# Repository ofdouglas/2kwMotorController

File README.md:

# 2kwMotorController
2 kilowatt brushed DC motor controller

This is a senior design project in Electrical and Computer Engineering at George Mason University.

All works are copyrighted by their respective authors.

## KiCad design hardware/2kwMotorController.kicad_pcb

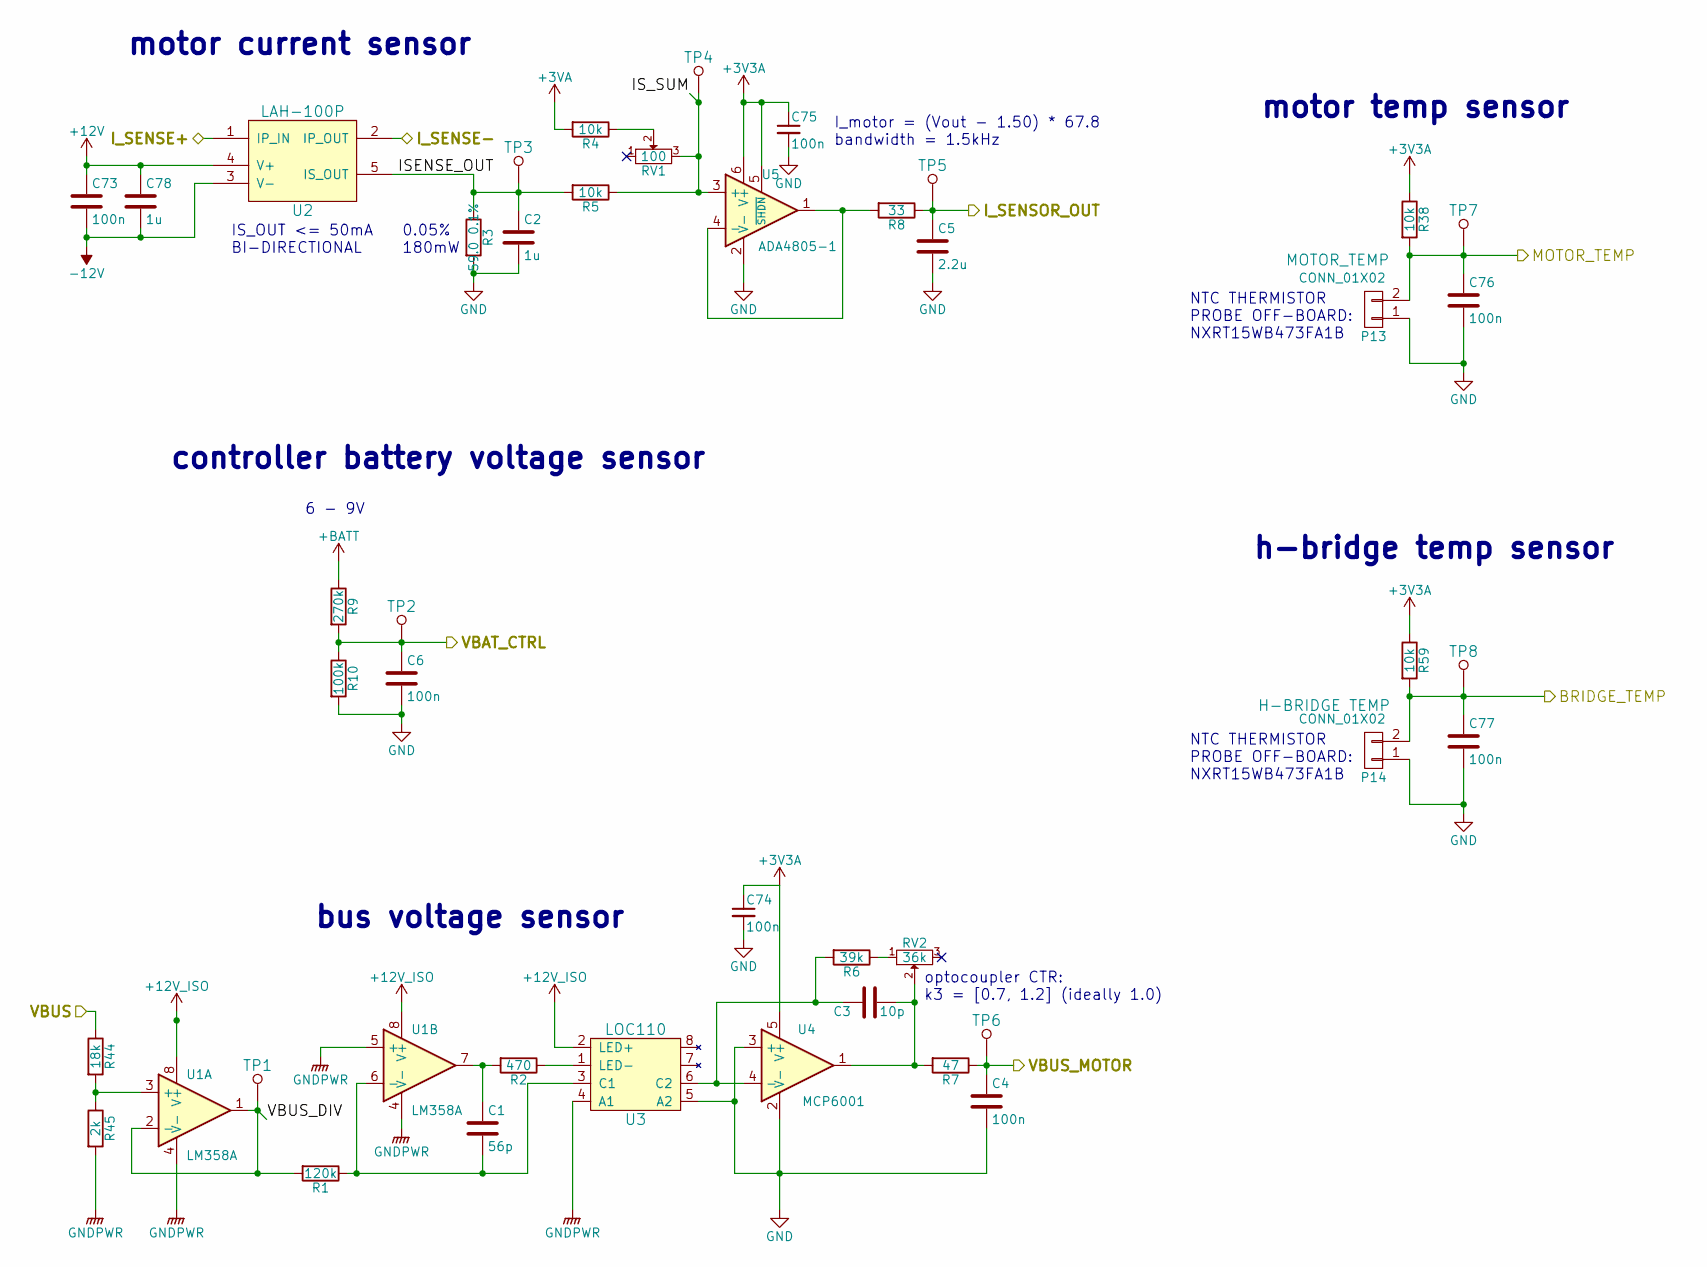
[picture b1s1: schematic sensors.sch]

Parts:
C1: 56p; C_0603; Voltage 16V
C2: 1u; C_0603; Voltage 16V
C3: 10p; C_0603; Voltage 16V
C4, C6, C74, C75, C76, C77: 100n; C_0603; Voltage 16V
C5: 2.2u; C_0603; Voltage 16V
C73: 100n; C_0603; Voltage 25V
C78: 1u; C_0603; Voltage 25V
P13, P14: CONN_01X02; Pin_Header_Straight_1x02
R1: 120k; R_0603
R2: 470; R_0603
R3: 59.0 0.1%; R_1206
R4, R5, R38, R59: 10k; R_0603
R6: 39k; R_0603
R7: 47; R_0603
R8: 33; R_0603
R9: 270k; R_0603
R10: 100k; R_0603
R44: 18k; R_0603
R45: 2k; R_0603
RV1: 100; Trimpot-23B
RV2: 36k; Trimpot-23B
TP1, TP2, TP3, TP4, TP5, TP6, TP7, TP8: TEST_POINT; TEST_PAD_1.27mm
U1: LM358A; SOIC-8_3.9x4.9mm_Pitch1.27mm
U2: LAH-100P; LAH_100-P
U3: LOC110; DIP-8_SMD
U4: MCP6001; SC-70-5
U5: ADA4805-1; SOT-23-6

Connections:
+3V3A: C74.1, C75.1, R38.1, R59.1, U4.5 (V+), U5.5 (~SHDN), U5.6 (V+); also elsewhere on the board
+3VA: R4.2; also elsewhere on the board
+12V: C73.1, C78.1, U2.4 (V+); also elsewhere on the board
+12V_ISO: U1.8 (V+), U3.2 (LED+); also elsewhere on the board
+BATT: R9.1; also elsewhere on the board
-12V: C73.2, C78.2, U2.3 (V-); also elsewhere on the board
/h-bridge/I_SENSE+: U2.1 (IP_IN); also elsewhere on the board
/h-bridge/I_SENSE-: U2.2 (IP_OUT); also elsewhere on the board
/h-bridge/VBUS: R44.1; also elsewhere on the board
/mcu/BRIDGE_TEMP: C77.1, P14.2, R59.2, TP8.1; also elsewhere on the board
/mcu/I_SENSOR_OUT: C5.1, R8.1, TP5.1; also elsewhere on the board
/mcu/MOTOR_TEMP: C76.1, P13.2, R38.2, TP7.1; also elsewhere on the board
/mcu/VBAT_CTRL: C6.1, R9.2, R10.1, TP2.1; also elsewhere on the board
/mcu/VBUS_MOTOR: C4.1, R7.1, TP6.1; also elsewhere on the board
/sensors/ISENSE_OUT: C2.1, R3.1, R5.2, TP3.1, U2.5 (IS_OUT)
/sensors/IS_SUM: R5.1, RV1.3, TP4.1, U5.3 (+)
/sensors/VBUS_DIV: R1.2, TP1.1, U1.1, U1.2 (-)
GND: C2.2, C4.2, C5.2, C6.2, C74.2, C75.2, C76.2, C77.2, P13.1, P14.1, R3.2, R10.2, U3.5 (A2), U4.2 (V-), U4.3 (+), U5.2 (V-); also elsewhere on the board
GNDPWR: R45.2, U1.4 (V-), U1.5 (+), U3.4 (A1); also elsewhere on the board
unnamed: C1.1, R2.2, U1.7
unnamed: C1.2, R1.1, U1.6 (-), U3.3 (C1)
unnamed: C3.1, R6.2, U3.6 (C2), U4.4 (-)
unnamed: C3.2, R7.2, RV2.2, U4.1
unnamed: R2.1, U3.1 (LED-)
unnamed: R4.1, RV1.2
unnamed: R6.1, RV2.1
unnamed: R8.2, U5.1, U5.4 (-)
unnamed: R44.2, R45.1, U1.3 (+)

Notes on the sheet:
IS_OUT <= 50mA BI-DIRECTIONAL
motor current sensor
h-bridge temp sensor
controller battery voltage sensor
bus voltage sensor
6 - 9V
optocoupler CTR: k3 = [0.7, 1.2] (ideally 1.0)
I_motor = (Vout - 1.50) * 67.8 bandwidth = 1.5kHz
0.05% 180mW
motor temp sensor
NTC THERMISTOR PROBE OFF-BOARD: NXRT15WB473FA1B

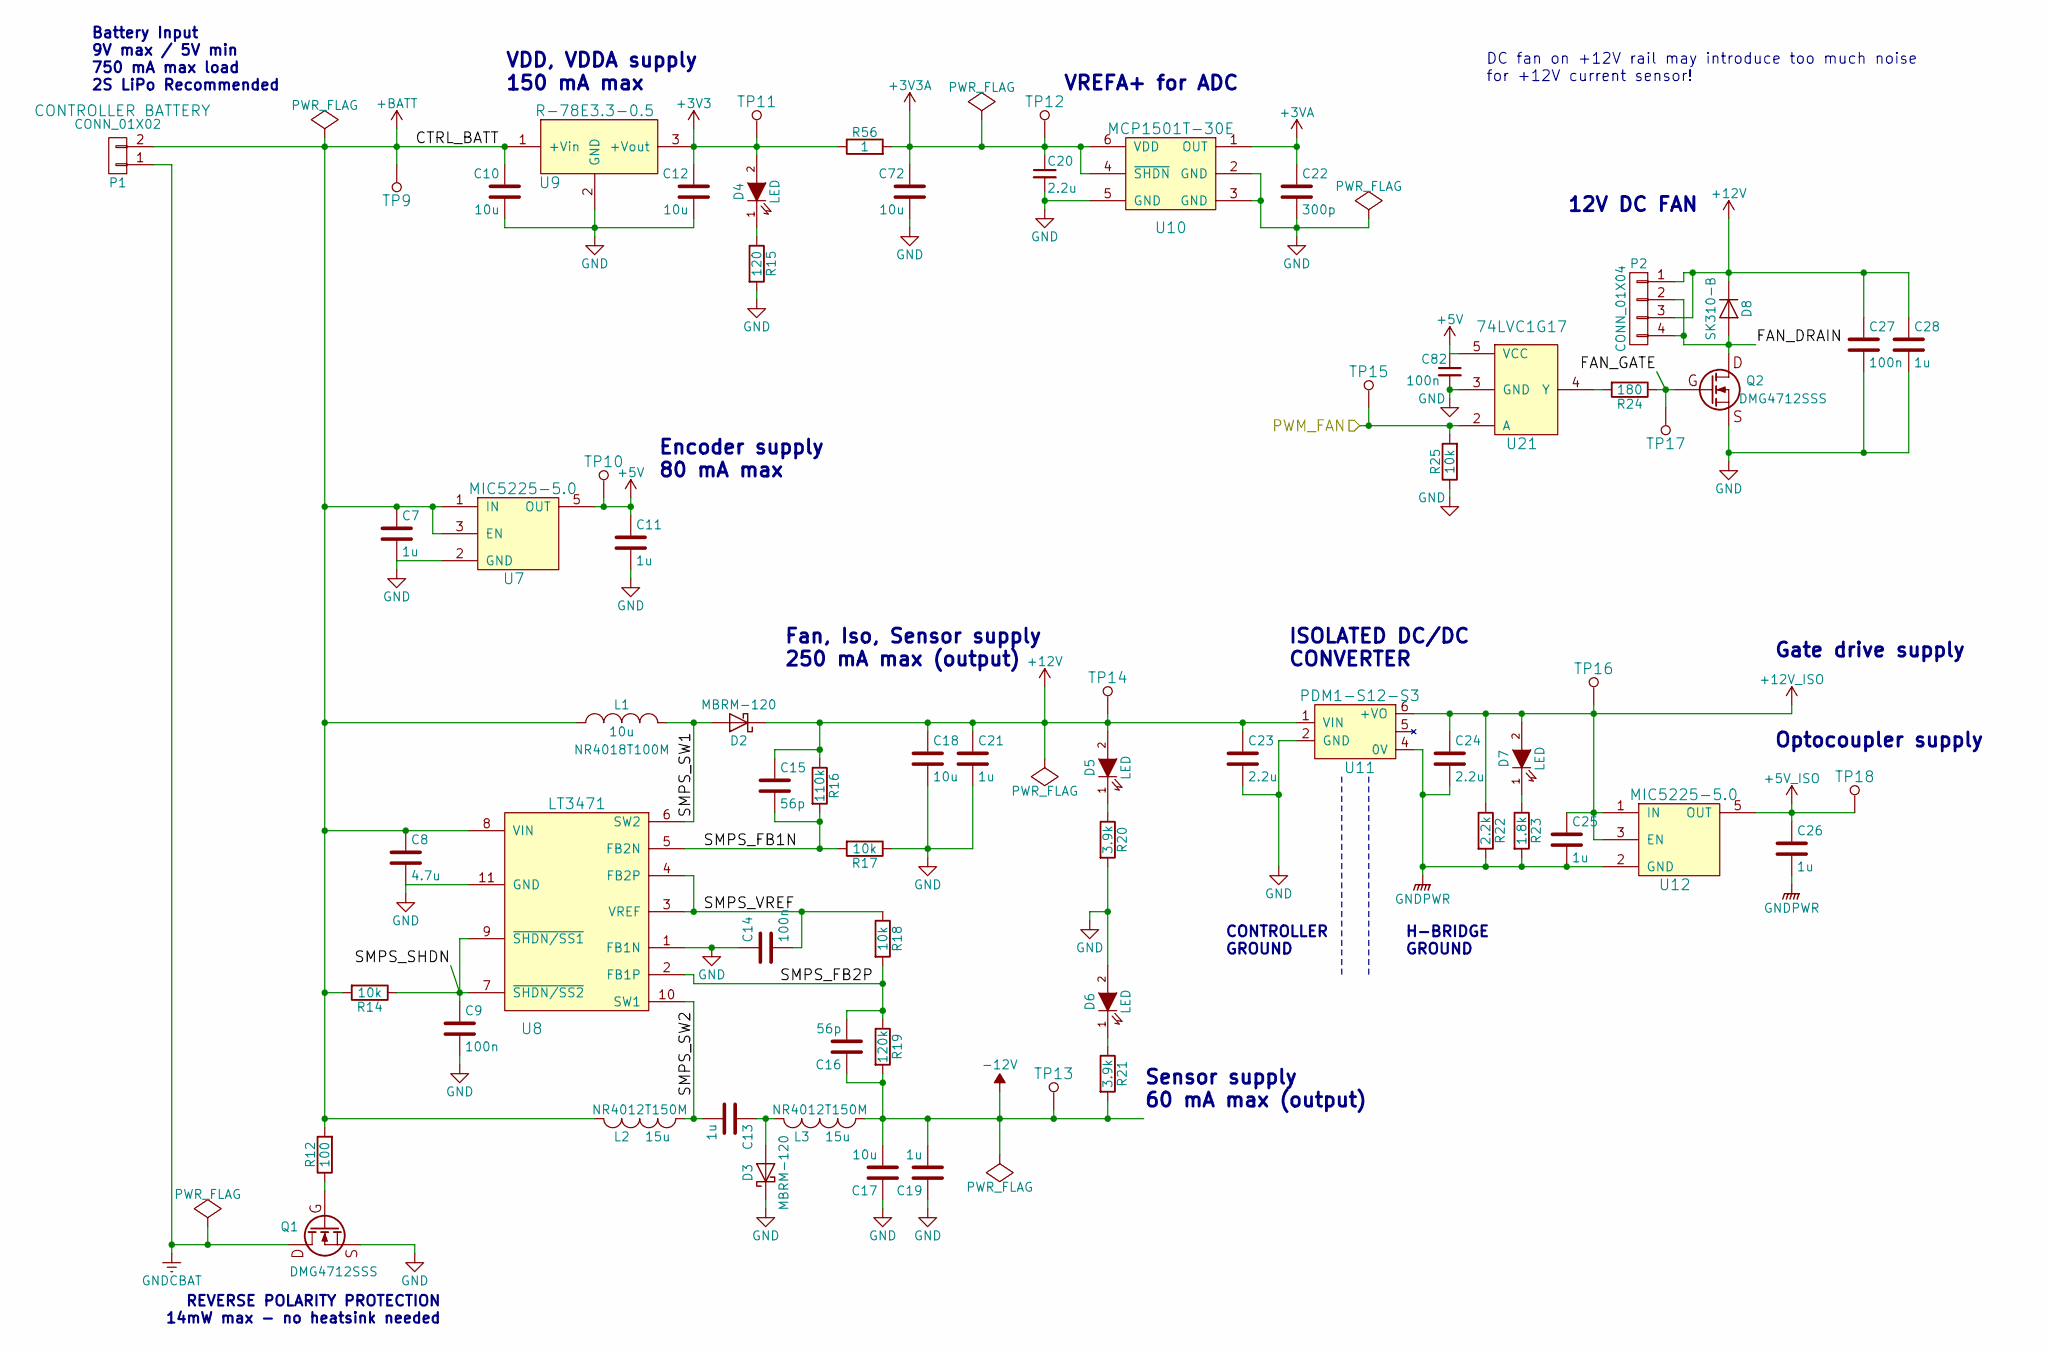
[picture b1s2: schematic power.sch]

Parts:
C7, C11: 1u; C_0603; Voltage 16V
C8: 4.7u; C_0603; Voltage 25V
C9, C14, C27, C82: 100n; C_0603; Voltage 25V
C10, C12, C72: 10u; C_0805; Voltage 16V
C13: 1u; C_0603
C15, C16: 56p; C_0603; Voltage 25V
C17, C18: 10u; C_0805; Voltage 25V
C19, C21, C25, C26, C28: 1u; C_0603; Voltage 25V
C20: 2.2u; C_0603; Voltage 16V
C22: 300p; C_0603; Voltage 16V
C23, C24: 2.2u; C_0603; Voltage 25V
D2, D3: MBRM-120; DIODE_POWERMITE
D4, D5, D6, D7: LED; LED_0603
D8: SK310-B; DIODE_POWERMITE
L1: 10u; INDUCTOR_NR40xx
L2, L3: 15u; INDUCTOR_NR40xx
P1: CONN_01X02; Pin_Header_Straight_1x02
P2: CONN_01X04; TERM_4P_2-4_1990025
Q1, Q2: DMG4712SSS; SOIC-8_3.9x4.9mm_Pitch1.27mm
R12: 100; R_0603
R14, R17, R18, R25: 10k; R_0603
R15: 120; R_0603
R16: 110k; R_0603
R19: 120k; R_0603
R20, R21: 3.9k; R_0603
R22: 2.2k; R_0603
R23: 1.8k; R_0603
R24: 180; R_0603
R56: 1; R_0603
TP9, TP10, TP11, TP12, TP13, TP14, TP15, TP16, TP17, TP18: TEST_POINT; TEST_PAD_1.27mm
U7, U12: MIC5225-5.0; SOT-23-5
U8: LT3471; DFN-10-1EP_3x3mm_Pitch0.5mm
U9: R-78E3.3-0.5; R-78E-0.5
U10: MCP1501T-30E; SOT-23-6
U11: PDM1-S12-S3; PDM2-S
U21: 74LVC1G17; SC-74A

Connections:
+3V3A: C20.1, C72.1, R56.2, TP12.1, U10.4 (~SHDN), U10.6 (VDD); also elsewhere on the board
+3VA: C22.1, U10.1 (OUT); also elsewhere on the board
+5V: C11.1, C82.1, TP10.1, U7.5 (OUT), U21.5 (VCC); also elsewhere on the board
+5V_ISO: C26.1, TP18.1, U12.5 (OUT); also elsewhere on the board
+12V: C15.1, C18.1, C21.1, C23.1, C27.1, C28.1, D2.1 (K), D5.2 (A), D8.1 (K), P2.1, P2.3, R16.1, TP14.1, U11.1 (VIN); also elsewhere on the board
+12V_ISO: C24.1, C25.1, D7.2 (A), R22.1, TP16.1, U11.6 (+VO), U12.1 (IN), U12.3 (EN); also elsewhere on the board
+BATT: C7.1, C8.1, C10.1, L1.1, L2.1, P1.2, R12.2, R14.2, TP9.1, U7.1 (IN), U7.3 (EN), U8.8 (VIN), U9.1 (+Vin); also elsewhere on the board
-12V: C16.1, C17.2, C19.2, L3.2, R19.2, R21.2, TP13.1; also elsewhere on the board
/mcu/PWM_FAN: R25.2, TP15.1, U21.2 (A); also elsewhere on the board
/power/FAN_DRAIN: D8.2 (A), P2.2, P2.4, Q2.5 (D), Q2.6 (D), Q2.7 (D), Q2.8 (D)
/power/FAN_GATE: Q2.4 (G), R24.1, TP17.1
/power/SMPS_FB1N: C15.2, R16.2, R17.2, U8.5 (FB2N)
/power/SMPS_FB2P: C16.2, R18.2, R19.1, U8.2 (FB1P)
/power/SMPS_SHDN: C9.1, R14.1, U8.7 (~SHDN/SS2), U8.9 (~SHDN/SS1)
/power/SMPS_SW1: D2.2 (A), L1.2, U8.6 (SW2)
/power/SMPS_SW2: C13.2, L2.2, U8.10 (SW1)
/power/SMPS_VREF: C14.2, R18.1, U8.3 (VREF), U8.4 (FB2P)
GND: C7.2, C8.2, C9.2, C10.2, C11.2, C12.2, C14.1, C17.1, C18.2, C19.1, C20.2, C21.2, C22.2, C23.2, C27.2, C28.2, C72.2, C82.2, D3.1 (K), D6.2 (A), Q1.1 (S), Q1.2 (S), Q1.3 (1), Q2.1 (S), Q2.2 (S), Q2.3 (1), R15.2, R17.1, R20.2, R25.1, U7.2 (GND), U8.1 (FB1N), U8.11 (GND), U9.2 (GND), U10.2 (GND), U10.3 (GND), U10.5 (GND), U11.2 (GND), U21.3 (GND); also elsewhere on the board
GNDCBAT: P1.1, Q1.5 (D), Q1.6 (D), Q1.7 (D), Q1.8 (D)
GNDPWR: C24.2, C25.2, C26.2, R22.2, R23.2, U11.4 (0V), U12.2 (GND); also elsewhere on the board
unnamed: C13.1, D3.2 (A), L3.1
unnamed: D4.1 (K), R15.1
unnamed: D5.1 (K), R20.1
unnamed: D6.1 (K), R21.1
unnamed: D7.1 (K), R23.1
unnamed: Q1.4 (G), R12.1
unnamed: R24.2, U21.4 (Y)

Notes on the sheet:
Battery Input 9V max / 5V min 750 mA max load 2S LiPo Recommended
REVERSE POLARITY PROTECTION 14mW max - no heatsink needed
H-BRIDGE GROUND
CONTROLLER GROUND
ISOLATED DC/DC CONVERTER
DC fan on +12V rail may introduce too much noise for +12V current sensor!
VREFA+ for ADC
VDD, VDDA supply 150 mA max
Fan, Iso, Sensor supply 250 mA max (output)
Sensor supply 60 mA max (output)
Optocoupler supply
Gate drive supply
Encoder supply 80 mA max
12V DC FAN

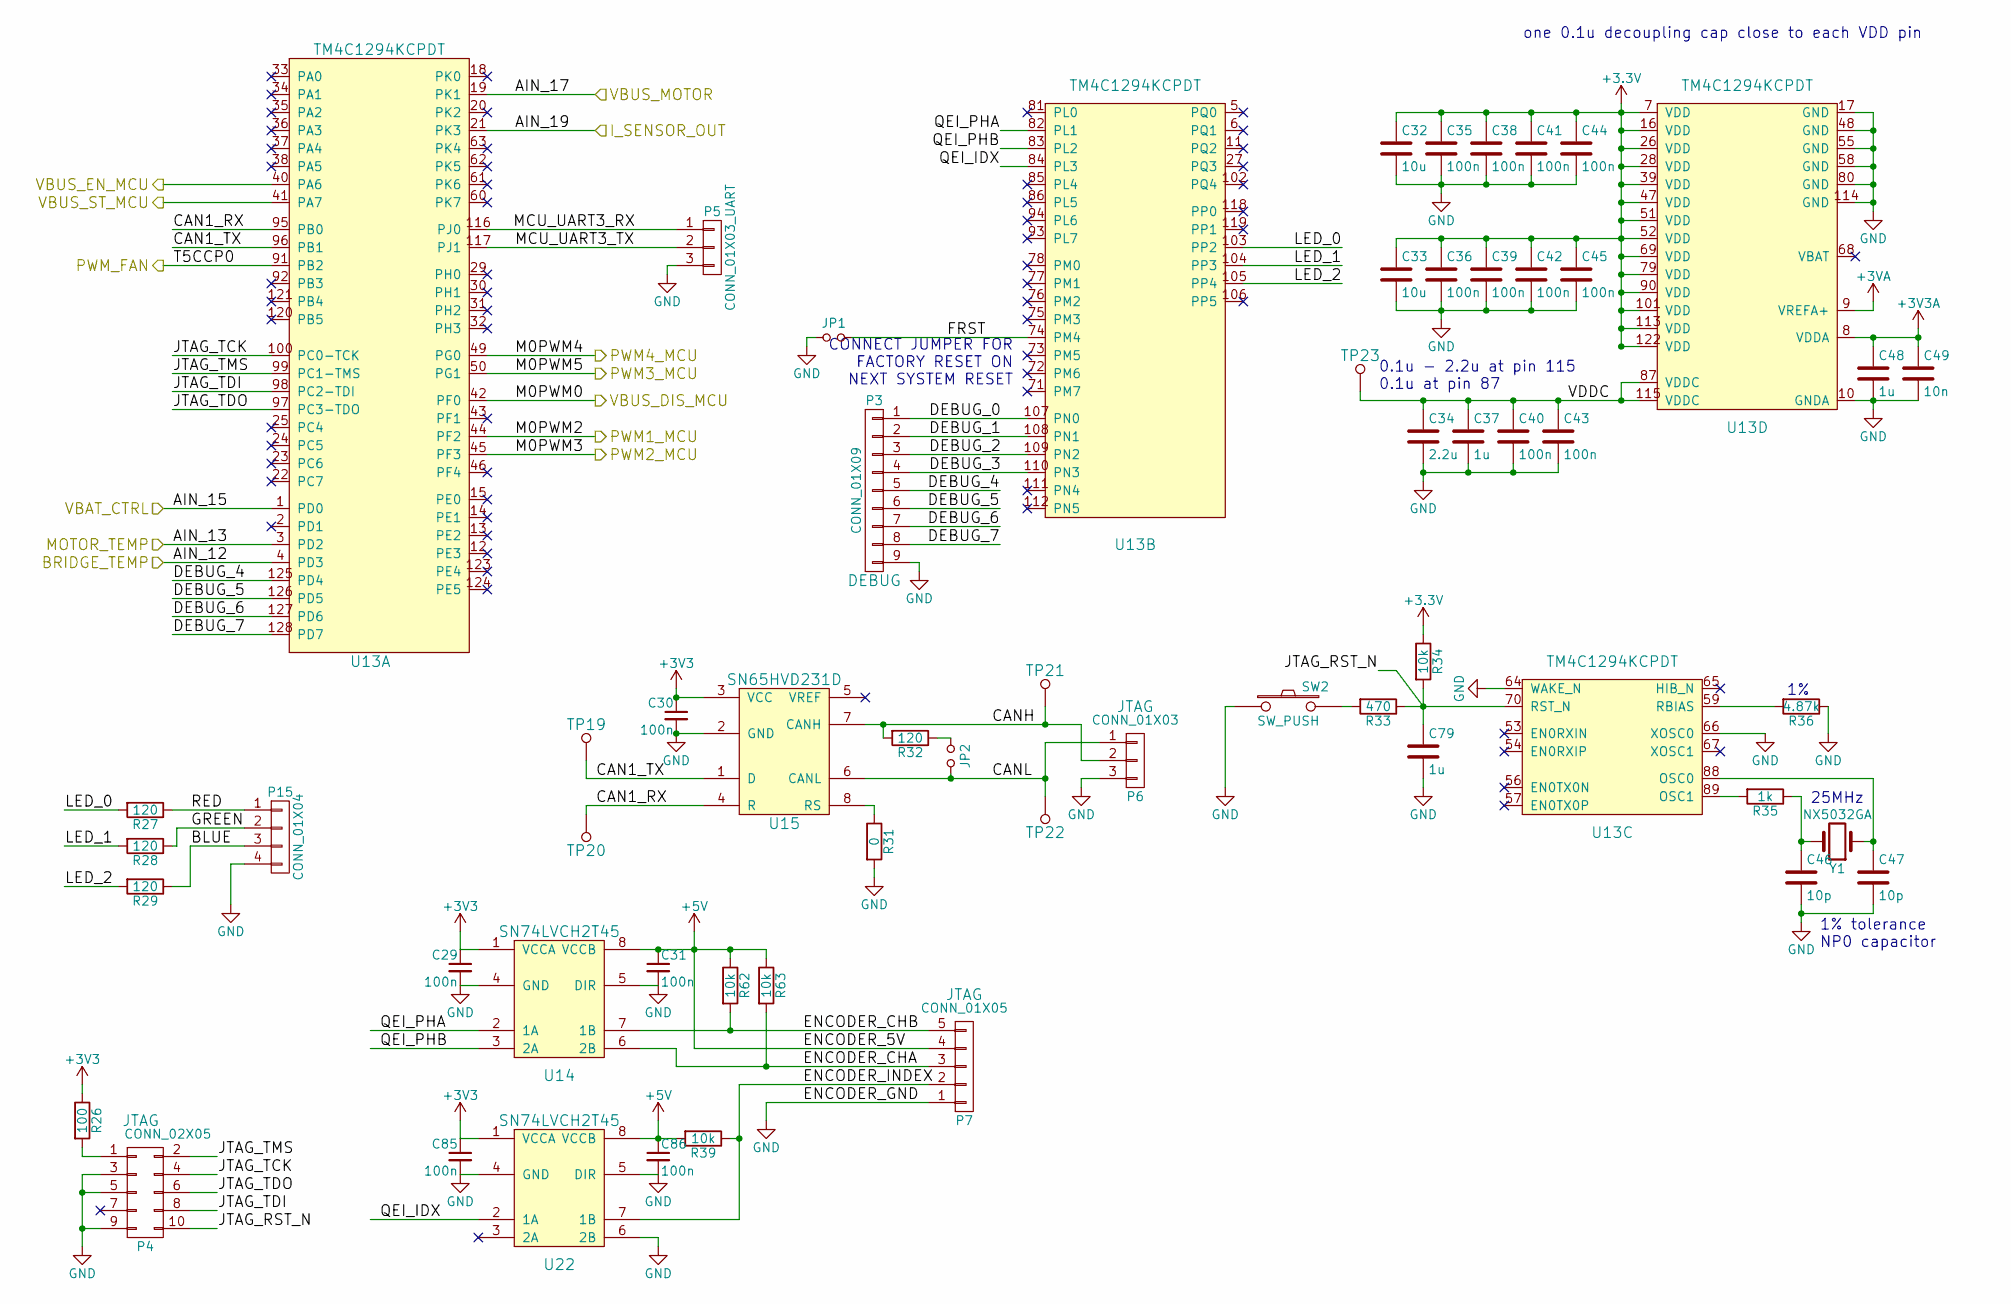
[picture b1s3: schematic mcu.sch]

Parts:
C29, C30, C31, C35, C36, C38, C39, C40, C41, C42, C43, C44, C45, C85, C86: 100n; C_0603; Voltage 16V
C32, C33: 10u; C_0805; Voltage 16V
C34: 2.2u; C_0603; Voltage 16V
C37, C48, C79: 1u; C_0603; Voltage 16V
C46, C47: 10p; C_0603; Voltage 16V
C49: 10n; C_0603; Voltage 16V
JP1, JP2: Jumper_NO_Small; Pin_Header_Straight_1x02
P3: CONN_01X09; Pin_Header_Straight_1x09
P4: CONN_02X05; Pin_Header_Straight_2x05_Pitch1.27mm
P5: CONN_01X03_UART; Pin_Header_Straight_1x03
P6: CONN_01X03; Pin_Header_Straight_1x03
P7: CONN_01X05; Pin_Header_Straight_1x05
P15: CONN_01X04; Pin_Header_Straight_1x04
R26: 100; R_0603
R27, R28, R29, R32: 120; R_0603
R31: 0; R_0603
R33: 470; R_0603
R34, R39, R62, R63: 10k; R_0603
R35: 1k; R_0603
R36: 4.87k; R_0603
SW2: SW_PUSH; SW_PUSH_SMALL
TP19, TP20, TP21, TP22, TP23: TEST_POINT; TEST_PAD_1.27mm
U13: TM4C1294KCPDT; TQFP-128_14x14mm_Pitch0.4mm_LONG
U14, U22: SN74LVCH2T45; MSOP-8_3x3mm_Pitch0.65mm
U15: SN65HVD231D; SOIC-8_3.9x4.9mm_Pitch1.27mm
Y1: NX5032GA; NX5032GA-CRYSTAL

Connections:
+3V3A: C48.1, C49.1, U13.8 (VDDA); also elsewhere on the board
+3VA: U13.9 (VREFA+); also elsewhere on the board
+5V: C31.1, C86.1, P7.4, R39.2, R62.1, R63.1, U14.8 (VCCB), U22.8 (VCCB); also elsewhere on the board
/h-bridge/PWM1_MCU: U13.44 (PF2); also elsewhere on the board
/h-bridge/PWM2_MCU: U13.45 (PF3); also elsewhere on the board
/h-bridge/PWM3_MCU: U13.50 (PG1); also elsewhere on the board
/h-bridge/PWM4_MCU: U13.49 (PG0); also elsewhere on the board
/h-bridge/VBUS_DIS_MCU: U13.42 (PF0); also elsewhere on the board
/h-bridge/VBUS_EN_MCU: U13.40 (PA6); also elsewhere on the board
/h-bridge/VBUS_ST_MCU: U13.41 (PA7); also elsewhere on the board
/mcu/BLUE: P15.3, R29.1
/mcu/BRIDGE_TEMP: U13.4 (PD3); also elsewhere on the board
/mcu/CAN1_RX: TP20.1, U13.95 (PB0), U15.4 (R)
/mcu/CAN1_TX: TP19.1, U13.96 (PB1), U15.1 (D)
/mcu/CANH: P6.2, R32.2, TP21.1, U15.7 (CANH)
/mcu/CANL: JP2.2, P6.1, TP22.1, U15.6 (CANL)
/mcu/DEBUG_0: P3.1, U13.107 (PN0)
/mcu/DEBUG_1: P3.2, U13.108 (PN1)
/mcu/DEBUG_2: P3.3, U13.109 (PN2)
/mcu/DEBUG_3: P3.4, U13.110 (PN3)
/mcu/DEBUG_4: P3.5, U13.125 (PD4)
/mcu/DEBUG_5: P3.6, U13.126 (PD5)
/mcu/DEBUG_6: P3.7, U13.127 (PD6)
/mcu/DEBUG_7: P3.8, U13.128 (PD7)
/mcu/ENCODER_CHA: P7.3, R63.2, U14.6 (2B)
/mcu/ENCODER_CHB: P7.5, R62.2, U14.7 (1B)
/mcu/ENCODER_INDEX: P7.2, R39.1, U22.7 (1B)
/mcu/FRST: JP1.1, U13.74 (PM4)
/mcu/GREEN: P15.2, R28.1
/mcu/I_SENSOR_OUT: U13.21 (PK3); also elsewhere on the board
/mcu/JTAG_RST_N: C79.1, P4.10, R33.1, R34.2, U13.70 (RST_N)
/mcu/JTAG_TCK: P4.4, U13.100 (PC0-TCK)
/mcu/JTAG_TDI: P4.8, U13.98 (PC2-TDI)
/mcu/JTAG_TDO: P4.6, U13.97 (PC3-TDO)
/mcu/JTAG_TMS: P4.2, U13.99 (PC1-TMS)
/mcu/LED_0: R27.2, U13.103 (PP2)
/mcu/LED_1: R28.2, U13.104 (PP3)
/mcu/LED_2: R29.2, U13.105 (PP4)
/mcu/MCU_UART3_RX: P5.1, U13.116 (PJ0)
/mcu/MCU_UART3_TX: P5.2, U13.117 (PJ1)
/mcu/MOTOR_TEMP: U13.3 (PD2); also elsewhere on the board
/mcu/PWM_FAN: U13.91 (PB2); also elsewhere on the board
/mcu/QEI_IDX: U13.84 (PL3), U22.2 (1A)
/mcu/QEI_PHA: U13.82 (PL1), U14.2 (1A)
/mcu/QEI_PHB: U13.83 (PL2), U14.3 (2A)
/mcu/RED: P15.1, R27.1
/mcu/VBAT_CTRL: U13.1 (PD0); also elsewhere on the board
/mcu/VBUS_MOTOR: U13.19 (PK1); also elsewhere on the board
/mcu/VDDC: C34.1, C37.1, C40.1, C43.1, TP23.1, U13.87 (VDDC), U13.115 (VDDC)
GND: C29.2, C30.2, C31.2, C32.2, C33.2, C34.2, C35.2, C36.2, C37.2, C38.2, C39.2, C40.2, C41.2, C42.2, C43.2, C44.2, C45.2, C46.2, C47.2, C48.2, C49.2, C79.2, C85.2, C86.2, JP1.2, P3.9, P4.3, P4.5, P4.9, P5.3, P6.3, P7.1, P15.4, R31.2, R36.1, SW2.1, U13.10 (GNDA), U13.17 (GND), U13.48 (GND), U13.55 (GND), U13.58 (GND), U13.64 (WAKE_N), U13.66 (XOSC0), U13.80 (GND), U13.114 (GND), U14.4 (GND), U14.5 (DIR), U15.2 (GND), U22.4 (GND), U22.5 (DIR), U22.6 (2B); also elsewhere on the board
unnamed: C46.1, R35.1, Y1.2
unnamed: C47.1, U13.88 (OSC0), Y1.1
unnamed: JP2.1, R32.1
unnamed: P4.1, R26.2
unnamed: R31.1, U15.8 (RS)
unnamed: R33.2, SW2.2
unnamed: R35.2, U13.89 (OSC1)
unnamed: R36.2, U13.59 (RBIAS)

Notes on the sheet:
0.1u - 2.2u at pin 115 0.1u at pin 87
one 0.1u decoupling cap close to each VDD pin
1% tolerance NP0 capacitor
25MHz
CONNECT JUMPER FOR FACTORY RESET ON NEXT SYSTEM RESET

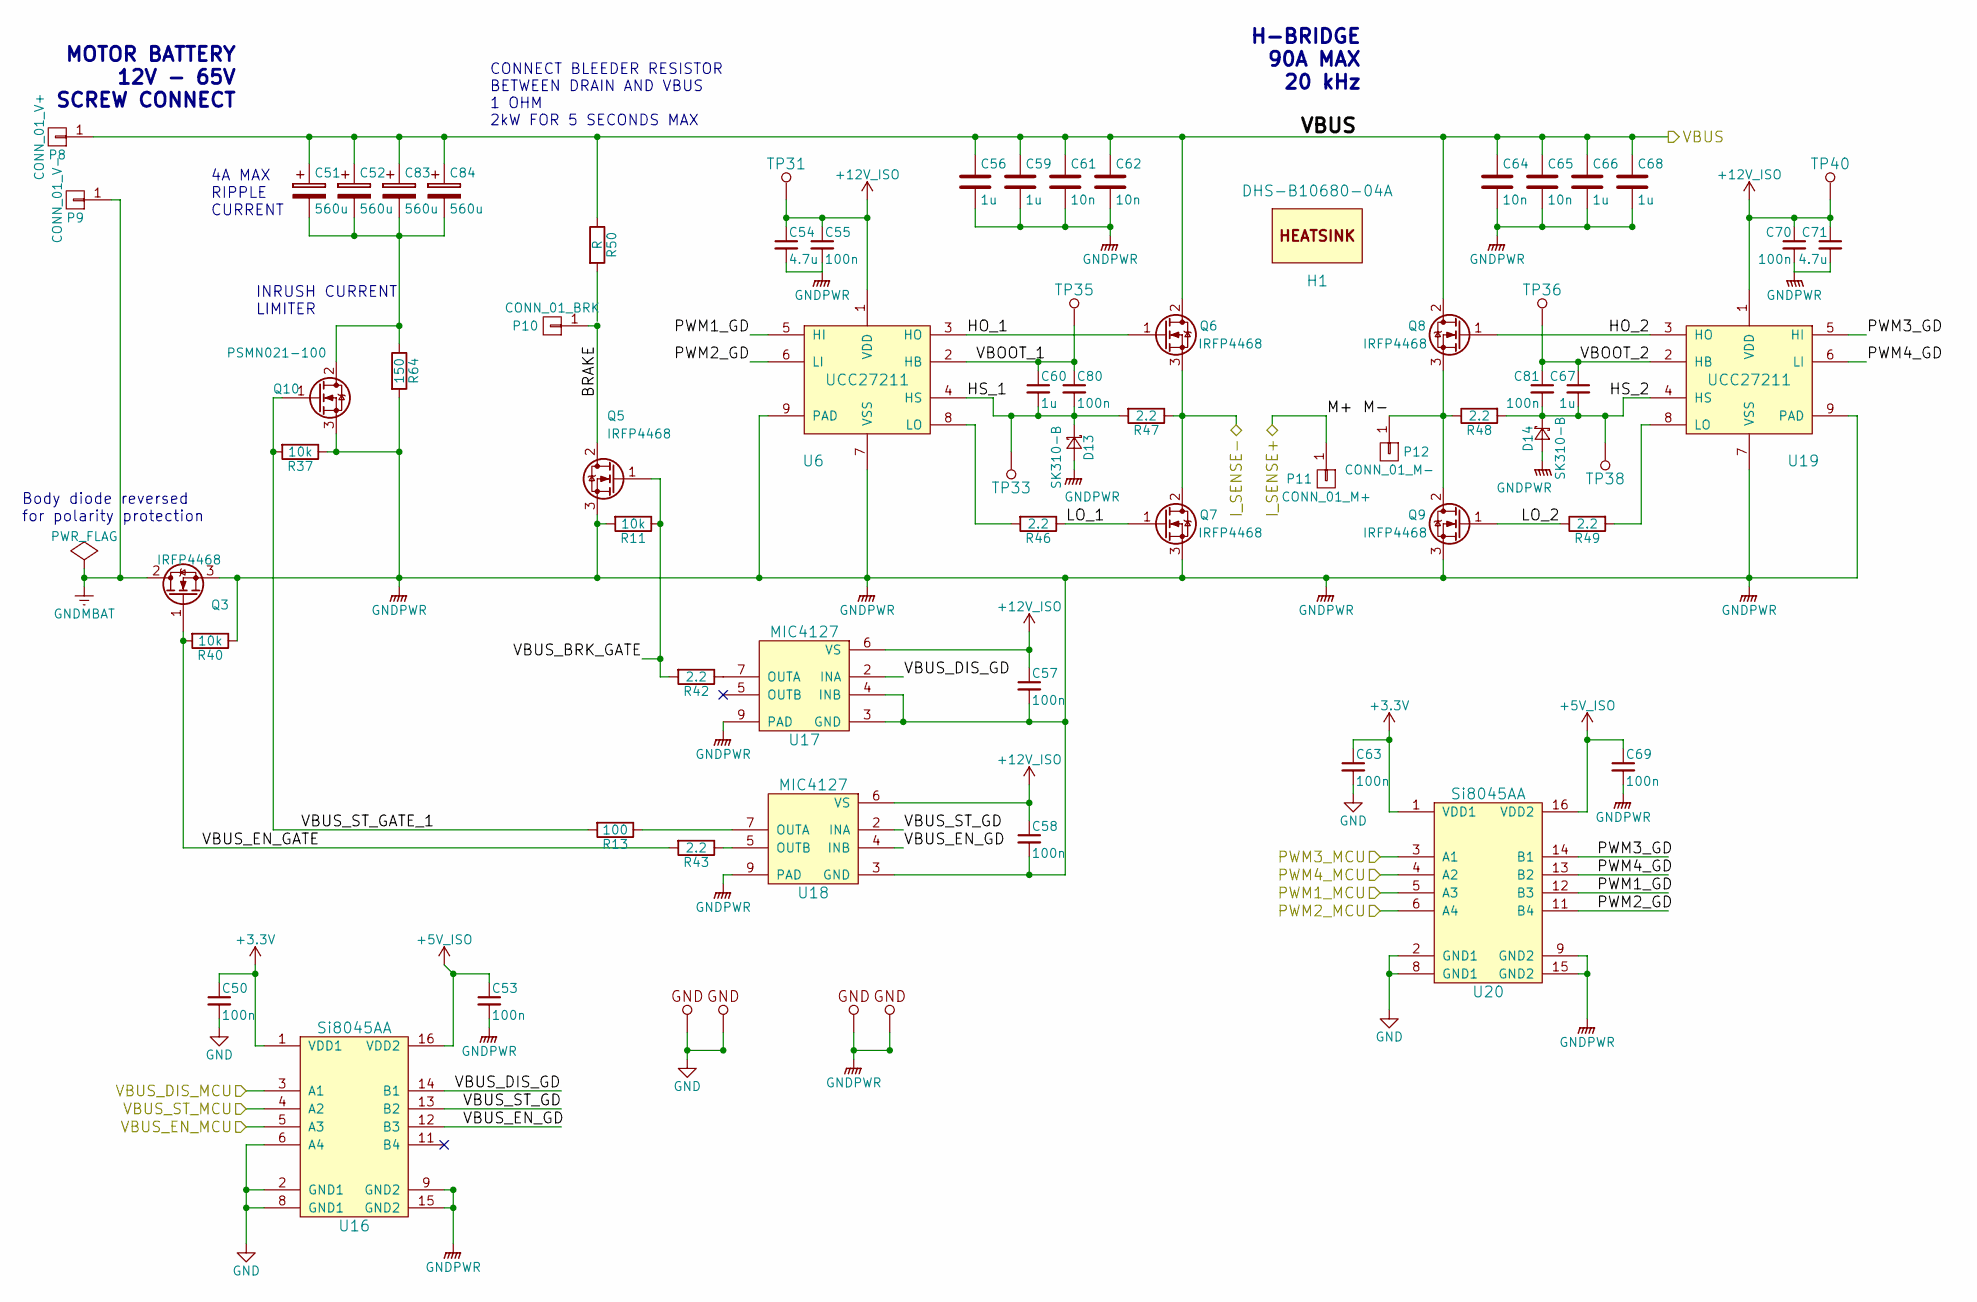
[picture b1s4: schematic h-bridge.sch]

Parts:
C50, C63: 100n; C_0603; Voltage 16V
C51, C52, C83, C84: 560u; CP18
C53, C55, C57, C58, C69, C70, C80, C81: 100n; C_0603; Voltage 25V
C54, C71: 4.7u; C_0805; Voltage 25V
C56, C59, C66, C68: 1u; C_1206; Voltage 100V
C60, C67: 1u; C_0603; Voltage 25V
C61, C62, C64, C65: 10n; C_0603; Voltage 100V
D13, D14: SK310-B; DO-214AA
GND1, GND2, GND8, GND9: GND_POINT; Pin_Header_Straight_1x01
H1: DHS-B10680-04A
P8: CONN_01_V+; M6_4AWG_LUG_TERM
P9: CONN_01_V-; M6_4AWG_LUG_TERM
P10: CONN_01_BRK; M6_4AWG_LUG_TERM
P11: CONN_01_M+; M6_4AWG_LUG_TERM
P12: CONN_01_M-; M6_4AWG_LUG_TERM
Q3, Q5, Q6, Q7, Q8, Q9: IRFP4468; TO-247_Horizontal_Neutral123_MountFromLS_largePads
Q10: PSMN021-100; SOT-669_LFPAK_ThermalVias-1
R11, R37, R40: 10k; R_0603
R13: 100; R_0603
R42, R43, R46, R47, R48, R49: 2.2; R_0603
R50: R
R64: 150; RESISTOR_FMP200
TP31, TP33, TP35, TP36, TP38, TP40: TEST_POINT; TEST_PAD_1.27mm
U6, U19: UCC27211; SOIC-8-1EP_3.9x4.9mm_Pitch1.27mm
U16, U20: Si8045AA; QSOP-16_3.9x4.9mm_Pitch0.635mm
U17, U18: MIC4127; SOIC-8-1EP_3.9x4.9mm_Pitch1.27mm

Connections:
+5V_ISO: C53.1, C69.1, U16.16 (VDD2), U20.16 (VDD2); also elsewhere on the board
+12V_ISO: C54.1, C55.1, C57.1, C58.1, C70.1, C71.1, TP31.1, TP40.1, U6.1 (VDD), U17.6 (VS), U18.6 (VS), U19.1 (VDD); also elsewhere on the board
/h-bridge/BRAKE: P10.1, Q5.2 (D)
/h-bridge/HO_1: Q6.1 (G), U6.3 (HO)
/h-bridge/HO_2: Q8.1 (G), U19.3 (HO)
/h-bridge/HS_1: C60.2, C80.2, D13.1 (K), R47.2, TP33.1, U6.4 (HS)
/h-bridge/HS_2: C67.2, C81.2, D14.1 (K), R48.2, TP38.1, U19.4 (HS)
/h-bridge/I_SENSE+: P11.1; also elsewhere on the board
/h-bridge/I_SENSE-: Q6.3 (S), Q7.2 (D), R47.1; also elsewhere on the board
/h-bridge/LO_1: Q7.1 (G), R46.1
/h-bridge/LO_2: Q9.1 (G), R49.1
/h-bridge/M-: P12.1, Q8.3 (S), Q9.2 (D), R48.1
/h-bridge/PWM1_GD: U6.5 (HI), U20.12 (B3)
/h-bridge/PWM1_MCU: U20.5 (A3); also elsewhere on the board
/h-bridge/PWM2_GD: U6.6 (LI), U20.11 (B4)
/h-bridge/PWM2_MCU: U20.6 (A4); also elsewhere on the board
/h-bridge/PWM3_GD: U19.5 (HI), U20.14 (B1)
/h-bridge/PWM3_MCU: U20.3 (A1); also elsewhere on the board
/h-bridge/PWM4_GD: U19.6 (LI), U20.13 (B2)
/h-bridge/PWM4_MCU: U20.4 (A2); also elsewhere on the board
/h-bridge/VBOOT_1: C60.1, C80.1, TP35.1, U6.2 (HB)
/h-bridge/VBOOT_2: C67.1, C81.1, TP36.1, U19.2 (HB)
/h-bridge/VBUS: C51.1, C52.1, C56.1, C59.1, C61.1, C62.1, C64.1, C65.1, C66.1, C68.1, C83.1, C84.1, P8.1, Q6.2 (D), Q8.2 (D), R50.1; also elsewhere on the board
/h-bridge/VBUS_BRK_GATE: Q5.1 (G), R11.1, R42.2
/h-bridge/VBUS_DIS_GD: U16.14 (B1), U17.2 (INA)
/h-bridge/VBUS_DIS_MCU: U16.3 (A1); also elsewhere on the board
/h-bridge/VBUS_EN_GATE: Q3.1 (G), R40.2, R43.2
/h-bridge/VBUS_EN_GD: U16.12 (B3), U18.4 (INB)
/h-bridge/VBUS_EN_MCU: U16.5 (A3); also elsewhere on the board
/h-bridge/VBUS_ST_GATE_1: Q10.1 (G), R13.2, R37.2
/h-bridge/VBUS_ST_GD: U16.13 (B2), U18.2 (INA)
/h-bridge/VBUS_ST_MCU: U16.4 (A2); also elsewhere on the board
GND: C50.2, C63.2, GND1.1, GND2.1, U16.2 (GND1), U16.6 (A4), U16.8 (GND1), U20.2 (GND1), U20.8 (GND1); also elsewhere on the board
GNDMBAT: P9.1, Q3.2 (D)
GNDPWR: C53.2, C54.2, C55.2, C56.2, C57.2, C58.2, C59.2, C61.2, C62.2, C64.2, C65.2, C66.2, C68.2, C69.2, C70.2, C71.2, D13.2 (A), D14.2 (A), GND8.1, GND9.1, Q3.3 (S), Q5.3 (S), Q7.3 (S), Q9.3 (S), Q10.3 (S), R11.2, R37.1, R40.1, R64.2, U6.7 (VSS), U6.9 (PAD), U16.9 (GND2), U16.15 (GND2), U17.3 (GND), U17.4 (INB), U17.9 (PAD), U18.3 (GND), U18.9 (PAD), U19.7 (VSS), U19.9 (PAD), U20.9 (GND2), U20.15 (GND2); also elsewhere on the board
unnamed: C51.2, C52.2, C83.2, C84.2, Q10.2 (D), R64.1
unnamed: R13.1, U18.7 (OUTA)
unnamed: R42.1, U17.7 (OUTA)
unnamed: R43.1, U18.5 (OUTB)
unnamed: R46.2, U6.8 (LO)
unnamed: R49.2, U19.8 (LO)

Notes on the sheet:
MOTOR BATTERY 12V - 65V SCREW CONNECT
CONNECT BLEEDER RESISTOR BETWEEN DRAIN AND VBUS 1 OHM 2kW FOR 5 SECONDS MAX
H-BRIDGE 90A MAX 20 kHz
Body diode reversed for polarity protection
INRUSH CURRENT LIMITER
4A MAX RIPPLE CURRENT

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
